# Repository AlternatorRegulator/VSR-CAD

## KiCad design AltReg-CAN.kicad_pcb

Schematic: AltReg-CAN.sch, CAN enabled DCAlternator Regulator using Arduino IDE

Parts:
Box1: CASE; HM1591xxB; Mouser 546-1591XXBSFLBK or 546-1591XXBFLBK(Fla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
C1: 4.7nF; SM0603_Capa; Part # 710-885012207070
C2, C5, C9, C10, C12, C13, C16, C17, C19, C20, C22, C25, C26, C27, C28: 100nF; SM0805; Part # 80-C0805C104K5R
C3: 22nF/200v; SM0805; Part # 603-CC805KKX7RABB223
C4, C29: 150pF; SM0805; Part # 581-08055C151K
C6, C7: 47pF; SM0603_Capa; Part # 77-VJ0603A470JXACBC
C14: 0.47uF; SM0805; Part # Optional: 603-CC805KKX7R8BB474
C15, C18, C24: 4.7uF; SM1206; Part # 81-GRM31CR71E475KA88
C21, C23, C30: 0.47uF; SM0805; Part # 603-CC805KKX7R8BB474
C31: 47uF/100v; CP_10x16mm; Part # 647-UPW2A470MPD
C32: 56uF; CP_6.3x11mm; Part # 647-UHD1V560MED
D1, D2, D18: SMAJ64A; do214ac; Part # 625-SMAJ64A-E3
D3, D4: CG0603MLC-05E; SM0603; Part # 652-CG0603MLC-05E
D5: SMAJ33A; do214ac; Part # 621-SMAJ33CA-13-F
D6, D9, D13, D15, D16: ESD5Z5.0T1G; sod523; Mouser 863-ESD5Z5.0T1G
D7, D11, D12: BAT54S; SOT23; Part # 863-BAT54SLT1G
D8, D19: FSV20100V; TO277-DIODE; Part # 512-FSV20100V
D10: 4.7v; SOT23; Mouser part# 863-BZX84C4V7LT1G
D14, D17: S110; sod123HE; Part # 512-S110FP
D20: SSA210; DO-214AC(SMA); Part # 512-SSA210
D21: NUP2105L; SOT23; Part # 863-NUP2105LT1G
D22: LED; LED-5MM-DUAL; Mouser 604-WP59EGW
D23, D24: 1N4148; sod123HE
J1: CS+Opt; Solder_trace
J2: I2C; PIN_ARRAY_2X1
J3: USB_MICRO; conn_usb_B_micro_vertical_TH
J4: USB_MICRO; conn_usb_B_micro_FCI_TOP
J5, J7: RJ45; RJ45_8; Part # 523-RJE081880110 or 649-54602-908LF
J6, J10: TERM; PIN_ARRAY_2X1
J8: GND-Opt; Solder_trace
J9: Alt+Opt; Solder_trace
L1: 10uH; SM0805; Part # 810-MLZ2012N100L
L2: 680uH; INDUCTOR_LRS; Part # 580-12LRS684C or 580-12LRS105C
L3: 1mH; inductor_smd_12x12mm; Part # 652-SRR1260-102K
P1: USB; PIN_ARRAY_5x1
P2: CONN_9; mkds_1,5-9; Mouser 651-1792931
P3: CONN_3; mkds_1,5-3; Part # 651-1792876
P4: ICSP; pin_array_3x2; Part # 649-67996-206HLF
P5: CAN; PCB_Terminal_3.81mm_3pin; Part # 158-P02EK381V3-E
P6: CONN_6; mkds_1,5-6; Part # 651-1935815
Q1: NZT605; sot223
Q2: T3904; SOT23; Part # 863-MMBT3904LT1G
Q3, Q4: TPW4R50ANH; DSOP-8; Part# 757-TPW4R50ANHL1Q
R1: 30K 0.1%; SM0805; Part # 603-RT0805BRD0730KL
R2, R9: 10; SM0603_Resistor; Part # 667-ERJ-3EKF10R0V
R3, R10: 0; SM0603_Resistor; Part # Optional: 660-RK73Z1JTTD
R4, R31: 30K; SM0603_Resistor; Mouser 71-CRCW0603-30K-E3
R5: 20K 0.1%; SM0805; Part # 603-RT0805BRD0720KL
R6, R23: 1M; SM0603_Resistor; Part # 603-RC0603FR-071ML
R7, R27, R30, R32, R33, R34, R41: 100; SM0603_Resistor; Part # 667-ERJ-3EKF1000V
R8, R22, R40, R42: 1K; SM0603_Resistor; Part # 667-ERJ-3EKF1001V
R11: 221; SM0603_Resistor; Part # 279-CPF0603B221RE1
R12, R13, R26, R29: 27; SM0603_Resistor; Part # 667-ERJ-3EKF27R0V
R14, R15: 4.99K; SM0603_Resistor; Part # 284-APC0603B4K99N
R16: 0; SM0603_Resistor; Part # 660-RK73Z1JTTD
R17, R19, R20, R21, R24, R35, R36, R37, R38, R39: 10K; SM0603_Resistor; Part # 667-ERJ-3EKF1002V
R18: 1K; SM0603_Resistor; Part # Optional: 667-ERJ-3EKF1001V
R25, R43, R44: 100K; SM0603_Resistor; Part # 667-ERJ-3EKF1003V
R28: 120; SM1210; Mouser 603-RC1210FR-07120RL
S1: SW_DIP-8; SWDIP8u; Part # 774-2108MS or 642-DPL08(right angle) or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
TH1: 10K NTC; SM0402; Part # 81-NCP15XH103F03RC
TP1: Vdd; PINTST
TP2: Sttr; TestPoint
TP3: Ena; TestPoint
TP4: GND; TestPoint
TP5: A; TestPoint
TP6: VB+; TestPoint
TP7: B; TestPoint
TP8: CS+; TestPoint
TP9: C; TestPoint
TP10: CS-; TestPoint
TP11: D; TestPoint
TP12: Fin; TestPoint
TP13: Fot; TestPoint
TP14: Vcc; PINTST
TP15: TMPA; TestPoint
TP16: TMPB; TestPoint
TP17: CH; TestPoint
TP18: CL; TestPoint
U1: NC7S14; SOT23-5; Part # 512-NC7S14M5X
U2: INA282; SO8E; Part # 595-INA282AIDR
U3: INA226; MSOP10-0.5; Part 3 595-INA226AIDGSR
U4: FT230X-S; ssop-16; Mouser Part# 895-FT230XS-R
U6: ATMEGA64M1-Ax; TQFP32; Part # 556-ATMEGA64M1-15AZ
U7: IRS21867; SOIC8; Mouser 942-IRS21867STRPBF
U8: MCP2562; SO8E
U9: MC78M05CDT; DPAK2; Part # 511-L78M05CDT-TR
U10: MAX5033D; SO8E; Mouser Part# 700-MAX5033DASA
V1, V2, V3, V4, V5, V6, V7, V8, V9, V10, V11, V12, V13, V14, V15, V16, V17, V18: VIA; 02mm_via
VAR1: 350mA; SM1812
X1: 16Mhz; resonator_smd

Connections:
+5V: C9.1, C16.2, C20.1, C22.1, C24.2, C26.1, C28.2, D7.2, D10.2, D11.2, D12.2, L1.2, P4.2, R14.1, R20.1, R21.1, R24.1, R25.2, R35.1, R36.1, R37.1, R38.1, TP14.1, U1.5 (Vcc), U2.3 (Ref_2), U2.7 (Ref1), U3.6 (Vss), U6.4 (VCC), U8.3 (Vdd), U8.5 (Vio), U9.3 (OUT)
/3.3v: C10.2, R17.1, U4.3 (VCCIO), U4.10 (3V3OUT), U4.11 (~RESET)
/A_NTC: R32.2, U6.13 ((PCINT21/ADC2/ACMP2)PD5)
/B: D8.1 (A), P6.3, Q3.2 (D), Q4.2 (D), TP7.1
/B_NTC: R34.2, U6.14 ((PCINT22/ADC3/INT0/ACMPN2)PD6)
/C: C18.1, D19.2 (K), P6.4, Q3.3 (S), Q4.3 (S), TP9.1, U7.6 (Vs)
/CAN-H: D21.1, J5.1, J6.2 (PM), J7.1, J10.2 (PM), P5.1, TP17.1, U8.7 (CANH)
/CAN-L: D21.2, J5.2, J7.2, P5.3, R28.2, TP18.1, U8.6 (CANL)
/CAN_GND: D24.1 (A), J5.3, J5.7, J7.3, J7.7
/CAN_V+: D23.2 (K), J5.8, J7.8
/CAN_shield: C14.1, J5.6, J7.6, P5.2 (PM)
/CSP+: C2.2, D2.2 (K), R2.2, R3.1, U2.8 (In+)
/CSP-: C2.1, D1.2 (K), R9.2, R10.1, U2.1 (In-)
/DIP-1: S1.1, U6.26 ((PCINT5/ADC6/INT2/ACMPN1/AMP2-)PB5)
/DIP-2: S1.2, U6.28 ((PCINT7/ADC4/SCK/PSCOUT0B)PB7)
/DIP-3: S1.3, U6.29 ((PCINT16/PSCOUT0A)PD0)
/DIP-4: S1.4, U6.18 ((PCINT13/ADC9/ACMP3/AMP1+)PC5)
/DIP-5: S1.5, U6.17 ((PCINT12/ADC8/ACMPN3/AMP1-)PC4)
/DIP-6: S1.6, U6.22 ((PCINT14/ADC10/ACMP1)PC6)
/DIP-7: S1.7, U6.16 ((PCINT2/ADC5/INT1/ACMPN0)PB2)
/DIP-8: S1.8, U6.15 ((PCINT23/ACMP0)PD7)
/FET_NTC: R24.2, TH1.2, U6.27 ((PCINT6/ADC7/PSCOUT1B)PB6)
/Feature_IN: R27.2, U6.24 ((PCINT4/AMP0+)PB4)
/Feature_OUT: R8.1, U6.23 ((PCINT3/AMP0-)PB3)
/Field PWM: U6.3 ((PCINT9/PSCIN1/OC1B/~SS_A~)PC1), U7.2 (HIN)
/HO: R26.2, R29.2, U7.7 (HO)
/HO-Q1: Q4.1 (G), R26.1
/HO-Q3: Q3.1 (G), R29.1
/Hb: C18.2, D17.2 (K), U7.8 (Vb)
/LED_Green: D13.2 (K), P4.1, R42.1, U6.1 ((PCINT18/PSCIN2/OC1A/MISO_A)PD2)
/LED_Red: R40.1, U6.32 ((PCINT17/CLKO/PSCIN0)PD1)
/POL-PROT: C31.1, D14.2 (K), U10.5 (On/~Off), U10.7 (Vin)
/SCL: J2.2 (PM), R37.2, U3.5 (SCL), U6.9 ((PCINT1/MOSI/PSCOUT2B)PB1)
/SDA: J2.1, R35.2, U3.4 (SDA), U6.8 ((PCINT0/MISO/PSCOUT2A)PB0)
/Stator_IRQ: U1.4 (Y), U6.30 ((PCINT8/INT3/PSCOUT1A)PC0)
/USB-SHLD: C1.2, J3.6, J4.6, P1.5, R6.2
/XD: C15.2, D12.3, J3.1, J4.1, P1.1, U4.12 (VCC)
/XE: D23.1 (A), VAR1.1
/XH: C27.2, C29.2, D20.2 (K), L2.1, L3.1, U10.8 (LX)
/~RESET: C13.2, D7.3, P4.5, R20.2, U6.31 ((PCINT24/OCD/~RESET~)PE0)
Alt+: D8.2 (K), J9.2, P6.1, P6.2, TP5.1
Alt-: D19.1 (A), J8.2, P6.5, P6.6, TP11.1
BAT-: C1.1, C4.1, C5.2, C6.1, C7.1, C9.2, C10.1, C12.2, C15.1, C16.1, C17.1, C19.1, C20.2, C21.2, C22.2, C23.2, C24.1, C25.2, C26.2, C28.1, C30.2, C31.2, C32.2, D1.1 (A), D2.1 (A), D3.1 (A), D4.1 (A), D5.1 (A), D6.1 (A), D7.1, D9.1 (A), D10.1, D11.1, D13.1 (A), D15.1 (A), D16.1 (A), D18.1 (A), D20.1 (A), D21.3, D22.K, D24.2 (K), J3.5, J4.5, J8.1, P1.4, P2.5, P4.6, Q1.3, R5.1, R6.1, R16.1, R18.2, R23.1, R30.2, R33.2, R39.2, R41.2, R44.1, S1.9, S1.10, S1.11, S1.12, S1.13, S1.14, S1.15, S1.16, TH1.1, TP4.1, U1.3 (GND), U2.2 (GND), U3.1 (A1), U3.2 (A0), U3.7 (GND), U4.5 (GND), U4.6 (~CTS), U4.13 (GND), U6.5 (GND), U6.20 (AGND), U7.3 (LIN), U7.4 (GND), U8.2 (Vss), U8.8 (STBY), U9.2 (GND), U10.3 (SGND), U10.6 (GND), V1.1, V2.1, V3.1, V4.1, V5.1, V6.1, V7.1, V8.1, V9.1, V10.1, V11.1, V12.1, V13.1, V14.1, V15.1, V16.1, V17.1, V18.1, X1.2
Current Shunt +: J1.1, P2.3, R2.1, R19.1, TP8.1
Current Shunt -: P2.2, R9.1, R19.2, TP10.1
Enable: D14.1 (A), D18.2 (K), P3.1, TP3.1
Feature-IN: P3.3, R4.1, TP12.1
Feature-OUT: P3.2 (PM), Q1.2, TP13.1
unnamed: C12.1, D11.3, R4.2, R23.2, R27.1
unnamed: U6.10 ((PCINT25/OC0B/XTAL1)PE1), X1.3
unnamed: U6.11 ((PCINT26/ADC0/XTAL2)PE2), X1.1
unnamed: C14.2, R18.1
unnamed: J3.4, J4.4
unnamed: J6.1, J10.1, R28.1
unnamed: U6.7 ((PCINT11/T1/ICP1B/RXCAN)PC3), U8.4 (RXD)
unnamed: U6.6 ((PCINT10/T0/TXCAN)PC2), U8.1 (TXD)
unnamed: R15.1, U2.5 (Out)
unnamed: C27.1, U10.1 (BST)
unnamed: J5.5, J7.5
unnamed: J5.4, J7.4
unnamed: D22.A1, R40.2
unnamed: P2.6, R33.1
unnamed: P2.8, R30.1
unnamed: D22.A2, R42.2
unnamed: C4.2, D5.2 (K), R1.2, R5.2, U3.8 (Vbus)
unnamed: R7.1, U1.2 (A)
unnamed: D10.3, R7.2, R31.1
unnamed: C3.2, R25.1, R31.2, R44.2
unnamed: C29.1, R41.1
unnamed: R16.2, U6.25 ((PCINT15/D2A/AMP2+)PC7)
unnamed: D6.2 (K), P4.4, U4.4 (RXD), U6.2 ((PCINT19/TXD/TXLIN/OC0A/~SS~/MOSI_A)PD3)
unnamed: Q1.1, R8.2
unnamed: R39.1, R43.1, U10.4 (FB)
unnamed: R10.2, R11.1, R14.2, U3.9 (Vin-)
unnamed: R3.2, R11.2, R15.2, U3.10 (Vin+)
unnamed: C25.1, U10.2 (VD)
unnamed: D9.2 (K), P4.3, R22.1, U6.12 ((PCINT20/ADC1/RXD/RXLIN/ICP1A/SCK_A)PD4)
unnamed: C6.2, D3.2 (K), J3.2, J4.2, P1.2, R12.1
unnamed: C7.2, D4.2 (K), J3.3, J4.3, P1.3, R13.1
unnamed: C17.2, U6.21 (AREF(ISRC))
unnamed: Q2.1 (B), R17.2
unnamed: Q2.2 (E), U4.2 (~RTS)
unnamed: R12.2, U4.9 (USBDM)
unnamed: R13.2, U4.8 (USBDP)
unnamed: R22.2, U4.1 (TXD)
unnamed: C13.1, Q2.3 (C), R21.2
unnamed: C19.2, L1.1, U6.19 (AVCC)
STATOR: C3.1, P2.1, TP2.1
TEMP-A: C23.1, D15.2 (K), P2.9, R32.1, R36.2, TP15.1
TEMP-B: C21.1, D16.2 (K), P2.7, R34.1, R38.2, TP16.1
VBat+: J1.2, J9.1, P2.4, R1.1, TP6.1
VDD: C5.1, C30.1, C32.1, D17.1 (A), L2.2, L3.2, R43.2, TP1.1, U2.6 (V+), U7.1 (Vdd), U9.1 (IN), VAR1.2

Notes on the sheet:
D12 allows configuration of unit via USB on bench
Dip 1..2 = CAN battery ID Dip 3..5 = Charge profile / Battery type Dip 6..7 = Bat Capacity Dip 8 = Small Alt Mode
P8 may be used to optionaly connect directly to wires, or a bulkhead connector (e.g. NMEA-2000). Ref CANopen spec CiA-303
Vdd = 13.4v
High Drive: A-jumper-B, C -field- D Low Drive: A -field- B, C-jumper-D
Design Point: 65v max Battery / System Voltage (32v max with '24v' stuffing option)
Q1/Q3 temp sensor
Stuffing Option - on-board USB
Note: When using RJ-45 connectors, "DMX Termination Plug" may be used for termination on end nodes
Option: Solder Jumpers to allow low wire count install See Users Manual.
Note: D20 & C32 are critical components. Take care with part # subs. See MAX5033D datasheet for details
Note: Configure uC to use external Vcc (5v) ADC Vref
Shield Gnd Populate R18, C14 only if needed
A-Temp: Alternator B-Temp: Battery, or optionaly 2nd alterantor (See users guide)
CAUTION: If J8 & J9 are bridged on PCB, do not install P2 Leaving the BAT- and VBat+ pins unaccessable.
24v - stuffing option: Install R3, R10, R16 Do not populate R11, R14, R15, R5, C5, U2 Change C4 to .1uF, change R1 to 10-ohms Change D1, D2 to SMAJ33CA (621-SMAJ33CA-13-F) Sysem max becomes 30V (battery target 24v max) R16 is used to signal to software this option is installed.
Diode D1 and D2 are uni-drection, they caused issues with LOW shunts and high ground offsets by starting to conduct around 500-600mV Consider repalcing with SMAJ62CA (bi-directional) devices...
'24v' signal to firmware

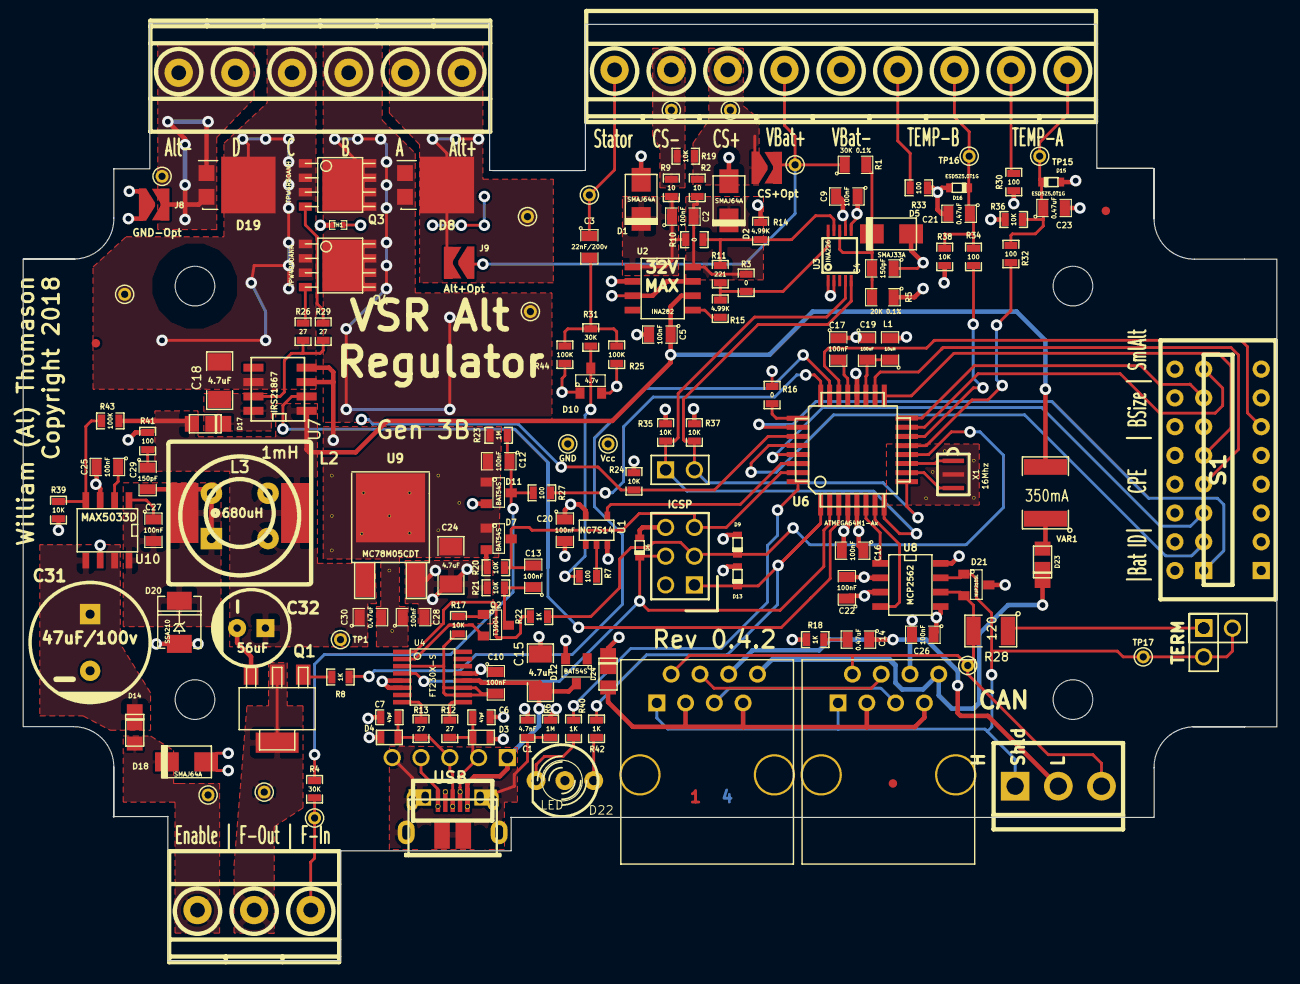
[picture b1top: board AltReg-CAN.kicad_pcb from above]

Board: 4 copper layers, 110.7 x 82.8 mm, 174 parts (0 on the bottom side), 92 nets.

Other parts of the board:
fiducial_075_300_round: FUD1; fiducial_075_300_round
fiducial_075_300_round#2: FUD3; fiducial_075_300_round
fiducial_075_300_round#3: FUD2; fiducial_075_300_round

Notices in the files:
AltReg-CAN.kicad_pcb:
Copyright 2018 -  William A. Thomason
Licensed under a Creative Commons Attribution-ShareAlike 4.0 International License.
